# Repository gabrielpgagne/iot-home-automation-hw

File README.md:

# iot-home-automation-hw
Home Automation project's Hardware files.

## Requirements

- Kicad 7.0
- DigiKey's Kicad Parts Library

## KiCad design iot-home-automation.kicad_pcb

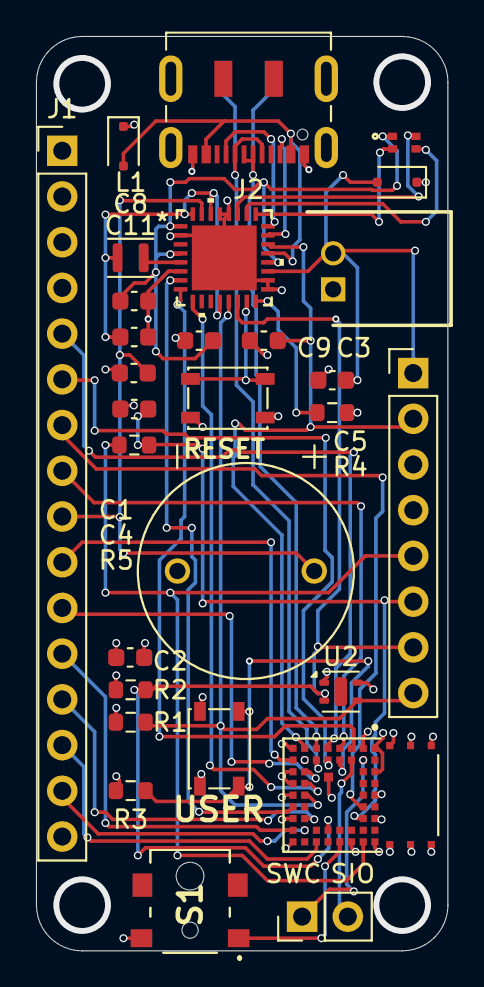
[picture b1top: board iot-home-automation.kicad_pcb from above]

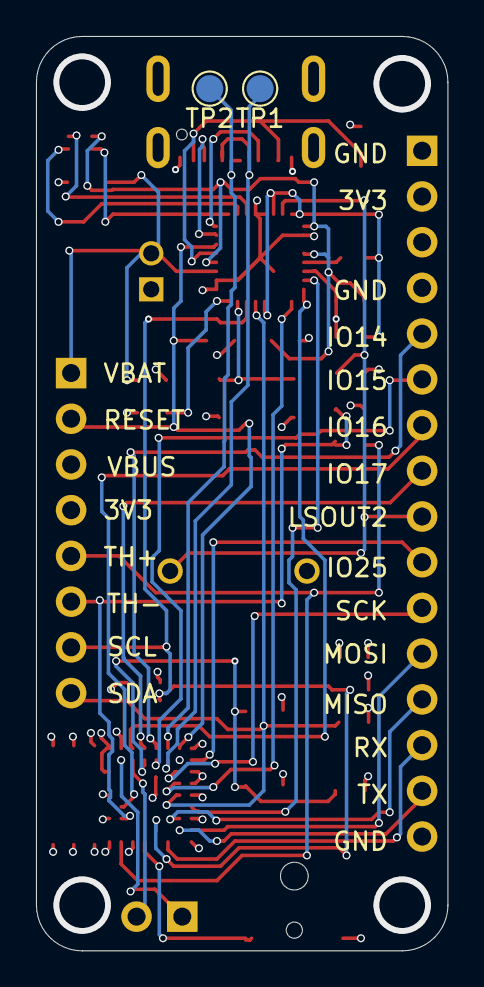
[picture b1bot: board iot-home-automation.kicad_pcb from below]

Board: 4 copper layers, 22.9 x 50.8 mm, 31 parts (2 on the bottom side), 38 nets.

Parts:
C1, C3: 1uF; C_0603_1608Metric
C2, C4: 0.1uF; C_0603_1608Metric
C5, C8, C9, C11: 10uF; C_0603_1608Metric
D1, D2: D_TVS; D_SOD-323F
J1: Conn_01x16_Female; PinHeader_1x16_P2.54mm_Vertical
J2: USB_C_Receptacle_USB2.0_16P; USB_C_Receptacle_JAE_DX07S016JA1R1500
J3: 440055-2; SHDRRA2W50P0X200_1X2_600X770X525P
J5: Conn_01x02_Pin; PinHeader_1x02_P2.54mm_Vertical
J6: Conn_01x08_Pin; PinHeader_1x08_P2.54mm_Vertical
L1: 2.2uH; L_Murata_DFE201610P
LED1: APHF1608LSEEQBDZGKC; APHF_KNB
LS1: AI-1223-TWT-3V-2-R; XDCR_AI-1223-TWT-3V-2-R
R1, R2, R3: 10K; R_0603_1608Metric
R4: 330K; R_0603_1608Metric
R5: 20K; R_0603_1608Metric
S1: CL-DA-1BB4-A2T; CLDA1BB4A2T
SW2, SW3: SW_Push; SW_SPST_PTS810
TP1, TP2: TestPoint; TestPoint_Pad_D1.5mm
U2: SHTC3; Sensirion_DFN-4-1EP_2x2mm_P1mm_EP0.7x1.6mm
U3: 453-00059R; XCVR_453-00059R
U4: NPM1300-QEAA-R7; QFN32_5X5_NOR

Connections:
+3V3: C2.1, C11.1, J1.2, J1.3, J6.4, L1.2, R1.1, R2.1, R3.1, U2.1 (VDD), U3.21 (VDD_NRF), U3.22 (VDD_HV), U3.30 (VDD_NRF_1), U4.12 (VDDIO), U4.30 (LSIN2/VINLDO2), U4.32 (VOUT2)
/CC1: J2.A5 (CC1), U4.23 (CC1)
/CC2: J2.B5 (CC2), U4.24 (CC2)
/D+: J2.A6 (D+), J2.B6 (D+), TP2.1, U3.26 (D+)
/D-: J2.A7 (D-), J2.B7 (D-), TP1.1, U3.49 (D-)
/DOOR_SW: S1.1, U3.12 (SIO_31/AIN7)
/GPIO0: U3.19 (SIO_11), U4.7 (GPIO0)
/GPIO1: U3.29 (SIO_12), U4.8 (GPIO1)
/GPIO2: U3.46 (SIO_13), U4.9 (GPIO2)
/IO14: J1.5, U3.27 (SIO_14)
/IO15: J1.6, U3.50 (SIO_15)
/IO16: J1.7, U3.35 (SIO_16)
/IO17: J1.8, U3.28 (SIO_17)
/IO25: J1.10, U3.23 (SIO_25)
/LED0: LED1.2, U4.25 (LED0)
/LED1: LED1.3, U4.26 (LED1)
/LED2: LED1.4, U4.27 (LED2)
/LSOUT2: C1.1, J1.9, LS1.P, U4.31 (LSOUT2/VOUTLDO2)
/MISO: J1.13, U3.43 (SIO_04/AIN2/SPI_MISO)
/MOSI: J1.12, U3.17 (SIO_40/SPI_MOSI)
/RX: J1.14, U3.14 (SIO_08/UART_RX)
/SCK: J1.11, U3.47 (SIO_41/SPI_CLK)
/SCL: J6.7, R2.2, U2.2 (SCL), U3.40 (SIO_27/I2C_SCL), U4.14 (SCL)
/SDA: J6.8, R1.2, U2.3 (SDA), U3.45 (SIO_26/I2C_SDA), U4.13 (SDA)
/SHPHLD: SW2.2, U4.15 (SHPHLD)
/SWDCLK: J5.1, U3.31 (SWDCLK)
/SWDIO: J5.2, U3.52 (SWDIO)
/TX: J1.15, U3.42 (SIO_06/UART_TX)
/USER_BTN: R3.2, SW3.2, U3.51 (SIO_32)
/VDD_TH: J6.5, R5.1, U3.10 (SIO_03/AIN1)
/VTH: C4.1, J6.6, R5.2, U3.36 (SIO_28/AIN4)
GND: C1.2, C2.2, C3.2, C4.2, C5.2, C8.2, C9.2, C11.2, D1.1 (A1), D2.1 (A1), J1.1, J1.4, J1.16, J2.A1 (GND), J2.A12 (GND), J2.B1 (GND), J2.B12 (GND), J2.S1 (SHIELD), J3.1, J6.3, LS1.N, R4.2, S1.3, SW2.1, SW3.1, U2.4 (VSS), U3.1 (GND), U3.3 (GND), U3.5 (GND), U3.7 (GND), U3.9 (GND), U3.11 (GND), U3.16 (GND), U3.18 (GND), U3.20 (GND), U3.24 (GND), U3.48 (GND), U3.G1 (GND), U3.G2 (GND), U3.G3 (GND), U3.G4 (GND), U3.G5 (GND), U3.G6 (GND), U3.G7 (GND), U4.2 (PVSS1), U4.6 (PVSS2), U4.17 (VSET1), U4.18 (NTC), U4.28 (LSIN1/VINLDO1), U4.29 (LSOUT1/VOUTLDO1), U4.33 (AVSS)
unnamed: L1.1, U4.5 (SW2)
unnamed: R4.1, U4.16 (VSET2)
VBAT: C5.1, D2.2 (A2), J3.2, J6.1, U4.19 (VBAT)
VBUSIN: D1.2 (A2), J2.A4 (VBUS), J2.A9 (VBUS), J2.B4 (VBUS), J2.B9 (VBUS), U4.21 (VBUS)
VBUSOUT: C3.1, J6.2, U3.25 (VBUS), U4.22 (VBUSOUT)
VSYS: C8.1, C9.1, LED1.1, U4.1 (VOUT1), U4.4 (PVDD), U4.20 (VSYS)

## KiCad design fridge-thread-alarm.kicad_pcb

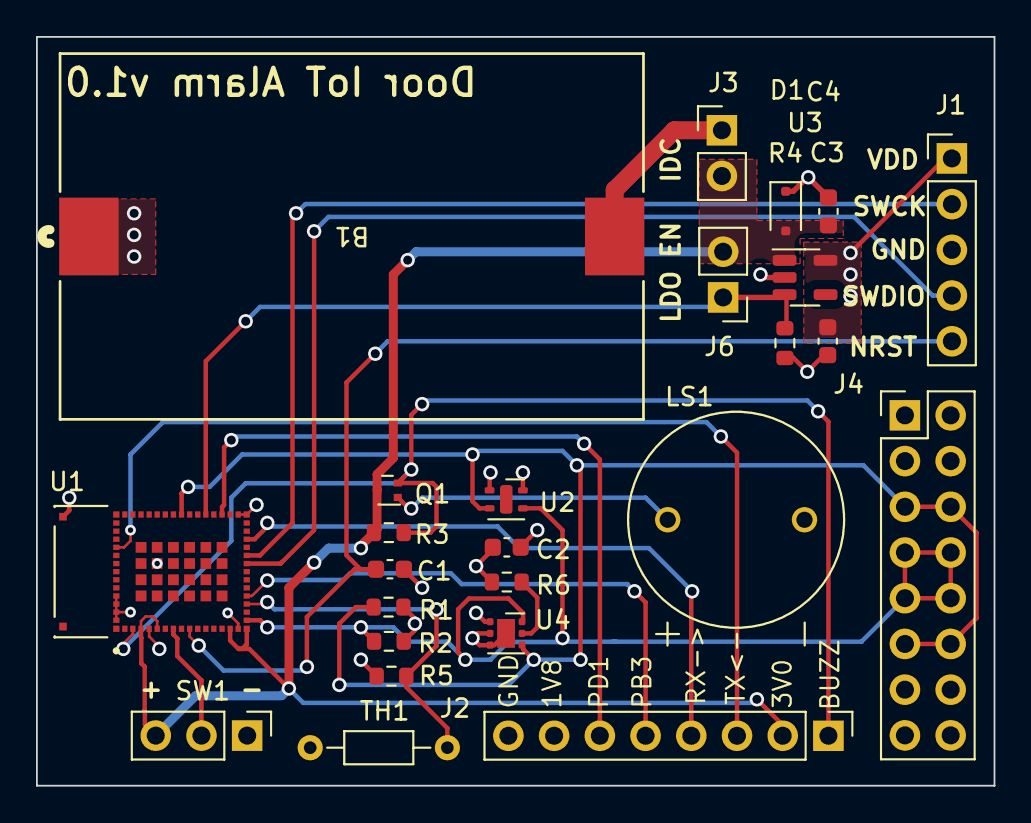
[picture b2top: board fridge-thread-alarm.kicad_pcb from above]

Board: 4 copper layers, 53.2 x 41.6 mm, 25 parts (0 on the bottom side), 19 nets.

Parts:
B1: BU2032SM-JJ-GTR; BU2032SM-JJ-GTR_MPD
C1, C2: 100nF; C_0603_1608Metric
C3, C4: 1uF; C_0603_1608Metric
D1: D_TVS; D_SOD-323F
J1: Conn_01x05_Pin; PinHeader_1x05_P2.54mm_Vertical
J2: Conn_01x08_Pin; PinHeader_1x08_P2.54mm_Vertical
J3, J6: Conn_01x02_Pin; PinHeader_1x02_P2.54mm_Vertical
J4: Conn_02x08_Odd_Even; PinHeader_2x08_P2.54mm_Vertical
LS1: AI-1223-TWT-3V-2-R; XDCR_AI-1223-TWT-3V-2-R
Q1: PMOS; SOT-723
R1, R2, R6: 10K; R_0603_1608Metric
R3, R4: 220K; R_0603_1608Metric
R5: 20K; R_0603_1608Metric
SW1: SW_Push_SPDT; PinHeader_1x03_P2.54mm_Vertical
TH1: 3.3K@25C; R_Axial_DIN0204_L3.6mm_D1.6mm_P7.62mm_Horizontal
U1: STM32WB5MMGH6TR; XCVR_STM32WB5MMGH6TR
U2: SHTC3; Sensirion_DFN-4-1EP_2x2mm_P1mm_EP0.7x1.6mm
U3: AP2127K-1.8; SOT-23-5
U4: OPT3001DNPT; WSON-6-1EP_2x2mm_P0.65mm_EP1x1.6mm

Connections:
+1V8: C2.1, C3.1, J1.1, J2.7, J4.3, J4.4, J4.13, J4.14, R1.1, R2.1, R5.1, R6.1, U2.1 (VDD), U3.5 (VOUT), U4.1 (VDD)
+3V0: C4.1, D1.2 (A2), J2.2, J3.2, J6.2, Q1.3 (S), R3.1, SW1.3 (C), U1.4 (VREF+), U1.6 (VDDA), U1.15 (VBAT), U1.17 (VDD), U3.1 (VIN)
+BATT: B1.2, J3.1
/Door_EXTI: SW1.2 (B), U1.8 (PC2)
/LDO_EN: J6.1, R4.1, U1.36 (PC6), U3.3 (EN)
/MCU_RX1: J2.4, U1.28 (PA10)
/MCU_TX1: J2.3, U1.51 (PA9)
/NRST: C1.1, J1.5, U1.10 (NRST)
/PB3: J2.5, U1.21 (PB3)
/PD1: J2.6, U1.34 (PD1)
/SCL1: J4.5, J4.6, J4.11, J4.12, R1.2, U1.39 (PB6), U2.2 (SCL), U4.4 (SCL)
/SDA1: J4.7, J4.8, J4.9, J4.10, R2.2, U1.18 (PB7), U2.3 (SDA), U4.6 (SDA)
/SWCLK: J1.2, U1.26 (PA14)
/SWDIO: J1.4, U1.25 (PA13)
/Vtherm: R5.2, TH1.1, U1.20 (PB4)
/nBuzzer: J2.1, Q1.2 (G), R3.2, U1.3 (PA0)
GND: B1.1, C1.2, C2.2, C3.2, C4.2, D1.1 (A1), J1.3, J2.8, J4.1, J4.2, J4.15, J4.16, LS1.N, R4.2, SW1.1 (A), TH1.2, U1.5 (VSS_0), U1.16 (VSS), U1.31 (VSS_1), U1.32 (VDDUSB), U1.57 (VSS_2), U1.58 (ANT_IN), U1.59 (RF_OUT), U1.60 (VSS_3), U1.84 (VSS_4), U1.86 (VSS_5), U2.4 (VSS), U3.2 (GND), U4.2 (ADDR), U4.3 (GND), U4.7 (PAD)
unnamed: LS1.P, Q1.1 (D)
unnamed: R6.2, U4.5 (INT)

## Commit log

2023-07-30 ADC1 pin correction
2023-07-30 removed doc folder
2023-07-30 Silkscreen errata
2023-08-19 sent for prod
2025-02-15 Schematic and first routing pass done
2025-02-15 Limit switch placement fixed
2025-03-13 Rev A
2025-04-27 RevB done?
2025-05-12 RevB done
2026-03-08 add 3d models
